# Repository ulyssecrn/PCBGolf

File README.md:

<div align="center">
<h1>My PCBGolf entry</h1>
<h3>comma.ai's PCBGolf challenge: a 4-port CAN-FD dev board on a 35 × 43 × 9.3 mm PCBA</h3>
<p>
  <a href="https://github.com/commaai/PCBGolf">Original challenge</a>
  <span> · </span>
  <a href="https://comma.ai/leaderboard#pcbgolf_challenge">Leaderboard</a>
  <span> · </span>
  <a href="https://kicanvas.org/?github=https%3A%2F%2Fgithub.com%2Fulyssecrn%2FPCBGolf%2Fblob%2Fmaster%2Fpcbgolf.kicad_pcb">View my layout in KiCanvas</a>
</p>
</div>

[PCBGolf](https://github.com/commaai/PCBGolf) is a challenge from comma.ai: take their reference board, loosely based on the panda jungle, and make the assembled PCBA as small as possible while keeping every interface working and every mating connector compatible. The board must be manufacturable and assemblable at JLCPCB. The score is

**bounding-box volume (mm³) + 50 × vias + 5,000 × copper layers**, lowest wins.

This repo is my submitted entry, finished on the October 12, 2026 deadline. The schematic is comma's. The layout, part choices and the design changes below are mine. comma's original README is kept unchanged [at the bottom](#original-challenge-readme).

## Result

| | |
|---|---|
| PCBA bounding box | 34.98 × 43.00 × 9.32 mm (includes the USB-C connector overhang) |
| Board outline | 33.9 × 42.3 mm, 0.79 mm thick |
| Copper layers | 4: signal / power / ground / signal |
| Vias | 303, all through-hole |
| Parts | 253, on both sides |
| **Score (by the formula)** | 14,027 + 15,150 + 20,000 = **≈ 49,200** |

The official score is assigned by comma after review.

<table>
  <tr>
    <td></td>
    <td></td>
  </tr>
  <tr>
    <td align="center">Top: connectors, CAN transceivers and chokes, power supplies</td>
    <td align="center">Bottom: STM32 (TFBGA-100), USB hub, microSD, port eFuses</td>
  </tr>
</table>

## What I changed

- **Stackup and placement.** 4 layers with an unbroken ground plane on In2. Parts on both sides: the STM32 and the USB hub on the bottom, the CAN transceivers and common-mode chokes on top, all six connectors on two edges.
- **MCU package: LQFP-144 → TFBGA-100.** I first tried the 7 × 7 mm UFBGA-169. At 0.5 mm pitch its inner balls carry signals and cannot be escaped on 4 layers without blind or buried vias. The 8 × 8 mm TFBGA-100 at 0.8 mm pitch escapes with ordinary dogbone vias.
- **Package change without touching the schematic.** The BGA footprint's pads are renamed to the LQFP-144 symbol's pin numbers, so comma's symbol keeps working and only the pins that don't exist on the smaller package needed rewiring.
- **Pin assignment as a routing tool.** Ports F and G aren't bonded out on TFBGA-100, so CAN2 moved to other FDCAN3 pins, and the SBU voltage-sense and current-monitor inputs moved to other ADC pins. I also re-ordered the 24 per-port control signals by channel so they leave the BGA in the same order as the connectors. All of this is a firmware pin-map change, which the rules allow (full table below).
- **Smaller parts.** 0201/0402 passives, 2016 crystals, smaller inductors, LEDs and dual FETs, a stemless 1.28 mm Molex microSD socket, and a TLV9101 (SC-70-5) in place of the SOT-23-5 op-amps that drive the CAN activity LEDs.

## Why the score isn't higher on the leaderboard

The penalties for layers and vias outweigh size. On this board, **layers (20,000) and vias (15,150) make up 71% of the score**, while the volume itself is only 14,027.

The top entries went the other way: one copper layer and no vias, with a board up to twice the area. Their fixed penalty is 5,000 instead of my 35,150. Once I had committed to a 4-layer board with a BGA, no amount of shrinking could close that gap. A 4-layer board scores 30,000+ before it has any volume at all.

**What I'd do differently:**
- Decide the layer count from the scoring formula first, and treat board area as the variable to give up.
- Pick an MCU package that can be routed on one or two layers (QFN/LQFP), even if it is larger.
- Watch the height. The DC barrel jack alone sets about 75% of the board's 9.3 mm height.

## Firmware changes

The MCU is an STM32H725VGH6 (TFBGA-100), the same die as the reference STM32H725ZGT (LQFP-144). Power, USB and clock setup are unchanged.

<details>
<summary>Pin map changes (reference → this board)</summary>

| Signal | Reference | This board | Notes |
|---|---|---|---|
| CAN2_TX / CAN2_RX | PG9 / PG10 | PD13 / PD12 | same FDCAN3 peripheral |
| BTN (GPIO read) | PE15 | PE5 | button still also drives BOOT0 |
| CH2_SBU2 sense | PF7 | PA3 | ADC12_INP15 (was ADC3) |
| CH4_SBU2 sense | PF8 | PA2 | ADC12_INP14 (was ADC3) |
| CH2_SBU1 sense | PF9 | PC5 | ADC12_INP8 (was ADC3) |
| CH4_SBU1 sense | PF10 | PB0 | ADC12_INP9 (was ADC3) |
| CH2_IMON | PB1 | PA6 | ADC12_INP3 |
| CH3_IMON | PF11 | PA5 | ADC12_INP19 |
| CH4_IMON | PA6 | PB1 | ADC12_INP5 |
| CH4_PWR_EN | PA5 | PA7 | |
| CH1_SBU1_IGN / RELAY | PD0 / PD1 | PD6 / PD3 | |
| CH1_SBU2_IGN | PD3 | PE0 | |
| CH2_SBU1_IGN / RELAY | PD5 / PD6 | PD1 / PE1 | |
| CH2_SBU2_IGN / RELAY | PD8 / PD10 | PD0 / PD5 | |
| CH3_SBU1_IGN / RELAY | PD12 / PD11 | PD14 / PD15 | |
| CH3_SBU2_IGN / RELAY | PD9 / PD13 | PE7 / PD11 | |
| CH4_SBU1_IGN / RELAY | PD14 / PD15 | PD9 / PE8 | |
| CH4_SBU2_IGN / RELAY | PE0 / PE1 | PD8 / PD10 | |

All other signals keep their reference pins.
</details>

## Files

- `pcbgolf.kicad_pro`: KiCad 10 project (the schematics are comma's, the layout is mine)
- `lib_jlc/`, `pcbgolf.pretty/`: footprints, symbols and 3D models; all paths are project-relative
- `assets/renders/`: the renders above, made with `kicad-cli pcb render`

<br>

---

*Everything below is comma.ai's original challenge README, unchanged.*

<div align="center">
<h1>PCBGolf Challenge</h1>
<h3>How small can you make this PCBA?</h3>
<h3>
  <a href="https://comma.ai/leaderboard#pcbgolf_challenge">Leaderboard</a>
  <span> · </span>
  <a href="https://comma.ai/jobs">comma.ai/jobs</a>
  <span> · </span>
  <a href="https://discord.comma.ai">Discord</a>
  <span> · </span>
  <a href="https://x.com/comma_ai">X</a>
</h3>
</div>

## The Board

The schematic is loosely based on [our panda jungle v2](https://www.comma.ai/shop/panda-jungle), a development and debugging board for comma devices and pandas. This version includes:

* 12V DC input with onboard 5V and 3.3V supplies
* Four [OBD-C](https://github.com/commaai/hardware/blob/master/harness/OBD-C.sch.pdf) device ports with individually controlled power and current monitoring
* Four CAN-FD transceivers and ignition simulation circuitry
* A USB hub and USB-C host connection
* A microcontroller and microSD card slot
* A push button and status LEDs

Explore in your browser with KiCanvas: [PCB layout](https://kicanvas.org/?github=https%3A%2F%2Fgithub.com%2Fcommaai%2FPCBGolf%2Fblob%2Fmaster%2Fpcbgolf.kicad_pcb).

Schematics: [Power](https://kicanvas.org/?github=https%3A%2F%2Fgithub.com%2Fcommaai%2FPCBGolf%2Fblob%2Fmaster%2Fpcbgolf.kicad_sch) · [Microcontroller](https://kicanvas.org/?github=https%3A%2F%2Fgithub.com%2Fcommaai%2FPCBGolf%2Fblob%2Fmaster%2Fpcbgolf_2.kicad_sch) · [USB & microSD](https://kicanvas.org/?github=https%3A%2F%2Fgithub.com%2Fcommaai%2FPCBGolf%2Fblob%2Fmaster%2Fpcbgolf_3.kicad_sch) · [CAN](https://kicanvas.org/?github=https%3A%2F%2Fgithub.com%2Fcommaai%2FPCBGolf%2Fblob%2Fmaster%2Fpcbgolf_4.kicad_sch) · [OBD-C ports](https://kicanvas.org/?github=https%3A%2F%2Fgithub.com%2Fcommaai%2FPCBGolf%2Fblob%2Fmaster%2Fpcbgolf_5.kicad_sch)

## The Challenge

Your goal is to make the most compact, efficient board that retains the same interfaces and functionality as the original design. The lowest score wins.

<p align="center">
  <picture>
    <source media="(prefers-color-scheme: dark)" srcset="./assets/score-dark.svg">
    
  </picture>
</p>

### Rules

* The bare PCB must be fully manufacturable by JLCPCB.
* It must be possible to actually assemble the PCBA.
* The assembled product must work and be usable.
* Mating connectors must remain mechanically and electrically compatible.
* Optimizations that require firmware changes are allowed.

### Prize

Lowest score on the [leaderboard](https://comma.ai/leaderboard#pcbgolf_challenge) by **October 12, 2026** wins **$1,000 cash**.

## Submission

Submit a `.zip` file containing your finalized KiCad project and a STEP file of the final assembly [here](https://forms.gle/US88Hg7UR6bBuW3BA).
Competitive scores will be posted on the [leaderboard](https://comma.ai/leaderboard#pcbgolf_challenge) after review. Multiple submissions allowed.

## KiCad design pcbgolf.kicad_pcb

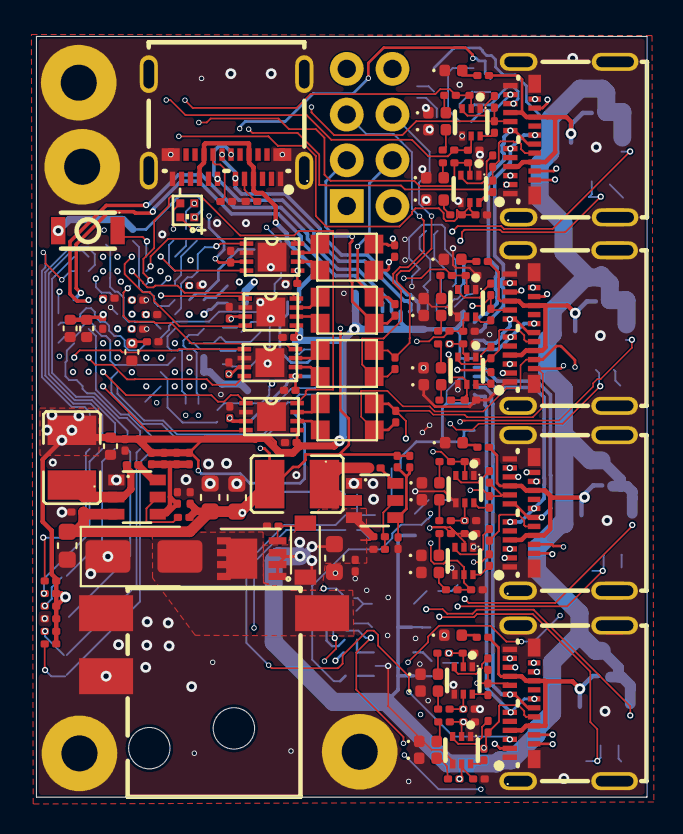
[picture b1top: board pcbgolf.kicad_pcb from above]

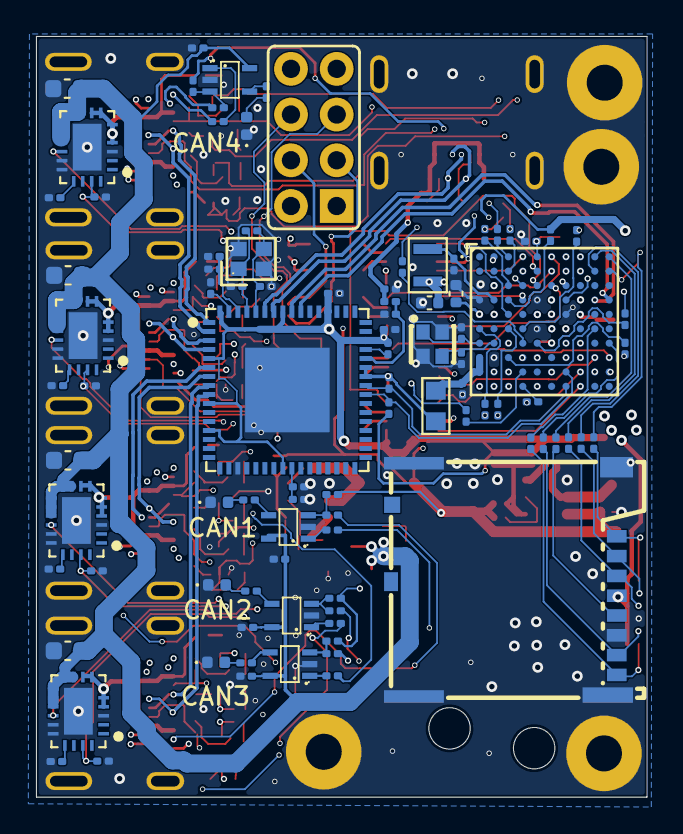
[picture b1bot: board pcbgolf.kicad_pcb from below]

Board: 4 copper layers, 33.9 x 42.3 mm, 253 parts (93 on the bottom side), 196 nets.

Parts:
BH1, BH2, BH3, BH4: M2_BOLT
C1, C3, C12, C13: 10uF; C_0603_1608Metric
C2, C4, C5, C7, C9, C11, C16, C18, C22, C23, C24, C26, C27, C30, C31, C35, C36, C38, C39, C40, C41, C42, C43, C44, C45, C46, C47, C48, C49, C55: 100nF; C_0201_0603Metric
C6, C10: DNP; C_0201_0603Metric
C8, C15, C19, C20, C21: 10uF; C_0402_1005Metric
C14, C17, C28, C32: 12pF; C_0201_0603Metric
C25: 220pF; C_0201_0603Metric
C29, C33, C34, C37: 10u; C_0201_0603Metric
C50, C51, C52, C53: 10u; C_0603_1608Metric
C54: 4.7uF; C_0402_1005Metric
D1: TVS-BI-DO214AA; D_SMA
D2: DIODEDB2W40100L; SOD-123F
J1: DCBARRELSMT; DC-IN-SMD_DC-044D-2.5A-2.0-SMT
J2: MICRO_SD-0472192001; microSD_Molex_5033981892
J3: USB-C-FEMALE; USB-C-J3-molex
J4: CAN; 2X04
J5, J6, J7, J8: USB-C-FEMALEGCT; USB-C-SMD_TYPE-C-USB-18
L1, L2: 3u3; IND_3225_3R3
L3: L-US-L2; 0603-L
L4: 2u2; 0806
L5, L6, L7, L8: ACT1210D_CHOKE; CHOKE-3.2X2.5
LED1: CREE-RGB-CLMVC; RGB_NH-B1010
LED2: CAN0; LED_0402_1005Metric
LED3: CAN1; LED_0402_1005Metric
LED4: CAN2; LED_0402_1005Metric
LED5: CAN3; LED_0402_1005Metric
LED6, LED7, LED8, LED9: CH1_PWR; LED_0402_1005Metric
LED10, LED11, LED12, LED13, LED14, LED15, LED16, LED17: LED_RED_0402; LED_0402_1005Metric
LED30, LED31, LED32, LED33, LED34, LED35, LED36, LED37: LED_GREEN_0402; LED_0402_1005Metric
Q1: SIS427-VI; PP-1212-8
Q2, Q3, Q4, Q5, Q6, Q7, Q8, Q9: NFET-DUAL-COMMON-SOURCE-QS5K2; SSM6N44FE-SOT563-remap
R1, R3, R7, R8, R9, R11, R12, R28, R29, R30, R33, R34, R35, R36, R37, R50, R51, R53, R54, R56, R57, R59, R60, R78, R79, R80, R81, R98, R99, R100, R101, R102, R103, R104, R105, R122, R123, R124, R125: 10k; R_0201_0603Metric
R2, R21, R23, R90, R92, R94, R96, R114, R116, R118, R120: 1k; R_0201_0603Metric
R4, R5, R6, R13, R14, R15, R16, R17, R18, R19, R20, R24, R25, R52, R55, R58, R61: 100k; R_0201_0603Metric
R10: 52k3; R_0201_0603Metric
R22, R62, R63, R64, R65: 2k7; R_0201_0603Metric
R26: 1M; R_0201_0603Metric
R27: 12k; R_0201_0603Metric
R32, R44: 5.1k; R_0201_0603Metric
R38, R39, R40, R41, R42, R43: 0R; R_0201_0603Metric
R46, R47, R48, R49: 60; R_0201_0603Metric
R66, R67, R68, R69: 28k; R_0201_0603Metric
R70, R71, R72, R73: 33k; R_0201_0603Metric
R74, R75, R76, R77: 3k3; R_0201_0603Metric
R82, R83, R84, R85, R86, R87, R88, R89, R91, R93, R95, R97, R106, R107, R108, R109, R110, R111, R112, R113, R115, R117, R119, R121: 100; R_0201_0603Metric
SW1: SPST-2-4PIN; SW_TS2306A
U1, U2: AP62300T; SOT23-6
U3: STM32H725VGH6; STM32H725-TFBGA100-remap
U4: USB2517; QFN64-9X9
U5, U6, U7, U8: MCP2542FDT-E/MNY; TDFN8_2X3MC_MCH
U13, U14, U15, U16: TPS25942; WQFN20
U17, U18, U19, U20: TLV9101IDCKR; TLV9101-SC70-5
Y1: 25MHz; Crystal_2016_25M
Y2: 24MHz; Crystal_2016_24M

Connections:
+3V3: C6.2, C7.1, C8.1, C19.1, C20.1, C23.1, C24.1, C26.1, C27.1, C30.2, C31.2, C37.1, C42.1, C43.1, C44.1, C45.1, C54.1, C55.1, J2.4 (VDD), L1.2, L3.1, LED1.U1 (COM+), R4.1, R5.1, R6.1, R11.1, R28.1, R29.1, R30.1, R33.1, R34.1, R35.1, R36.1, R37.1, SW1.B (S), SW1.B' (S1), U3.7 (VDD), U3.8 (VBAT), U3.13 (VDD), U3.16 (VDDSMPS), U3.19 (VDD), U3.91 (VDD33USB), U4.5 (VDDA33), U4.10 (VDDA33), U4.13 (CFG_SEL2), U4.24 (VDD33CR), U4.42 (CFG_SEL1), U4.43 (RESET_N), U4.46 (VDD33), U4.52 (VDDA33), U4.57 (VDDA33), U4.64 (VDD33PLL), U5.5 (VIO), U6.5 (VIO), U7.5 (VIO), U8.5 (VIO)
+5V: C1.1, C2.1, C10.2, C11.1, C12.1, C13.1, C38.1, C39.1, C40.1, C41.1, L2.2, R1.1, R10.2, R52.2, R55.2, R58.2, R61.2, U1.3 (IN), U5.3 (VDD), U6.3 (VDD), U7.3 (VDD), U8.3 (VDD)
+12V: C3.1, C5.1, C46.1, C47.1, C48.1, C49.1, C50.1, C51.1, C52.1, C53.1, D2.1 (C), Q1.1 (S), Q1.2 (S), Q1.3 (S), R7.1, U2.3 (IN), U13.9 (VIN), U13.10 (VIN), U13.11 (VIN), U13.12 (VIN), U13.13 (VIN), U14.9 (VIN), U14.10 (VIN), U14.11 (VIN), U14.12 (VIN), U14.13 (VIN), U15.9 (VIN), U15.10 (VIN), U15.11 (VIN), U15.12 (VIN), U15.13 (VIN), U16.9 (VIN), U16.10 (VIN), U16.11 (VIN), U16.12 (VIN), U16.13 (VIN), U17.5 (V+), U18.5 (V+), U19.5 (V+), U20.5 (V+)
BTN: R12.2, SW1.A, SW1.A' (P1), U3.4 (PE5), U3.135 (BOOT0)
CAN0_EN: U3.134 (PB7), U5.8 (STBY)
CAN0_H: J4.2, J5.A2 (TX1+), J6.A2 (TX1+), J7.A2 (TX1+), J8.A2 (TX1+), L5.4, R46.2, R50.1
CAN0_L: J4.1, J5.A3 (TX1-), J6.A3 (TX1-), J7.A3 (TX1-), J8.A3 (TX1-), L5.3, R46.1, R51.1
CAN0_RX: U3.136 (PB8), U5.4 (RXD)
CAN0_TX: U3.137 (PB9), U5.1 (TXD)
CAN1_EN: U3.130 (PB3(JTDO), U6.8 (STBY)
CAN1_H: J4.4, J5.A11 (RX2+), J6.A11 (RX2+), J7.A11 (RX2+), J8.A11 (RX2+), L6.4, R47.2, R53.1
CAN1_L: J4.3, J5.A10 (RX2-), J6.A10 (RX2-), J7.A10 (RX2-), J8.A10 (RX2-), L6.3, R47.1, R54.1
CAN1_RX: U3.132 (PB5), U6.4 (RXD)
CAN1_TX: U3.133 (PB6), U6.1 (TXD)
CAN2_EN: U3.121 (PD7), U7.8 (STBY)
CAN2_H: J4.6, J5.B2 (TX2+), J6.B2 (TX2+), J7.B2 (TX2+), J8.B2 (TX2+), L7.4, R48.2, R56.1
CAN2_L: J4.5, J5.B3 (TX2-), J6.B3 (TX2-), J7.B3 (TX2-), J8.B3 (TX2-), L7.3, R48.1, R57.1
CAN2_RX: U3.82 (PD12), U7.4 (RXD)
CAN2_TX: U3.83 (PD13), U7.1 (TXD)
CAN3_EN: U3.131 (PB4(NJTRST)), U8.8 (STBY)
CAN3_H: J4.8, J5.B11 (RX1+), J6.B11 (RX1+), J7.B11 (RX1+), J8.B11 (RX1+), L8.4, R49.2, R59.1
CAN3_L: J4.7, J5.B10 (RX1-), J6.B10 (RX1-), J7.B10 (RX1-), J8.B10 (RX1-), L8.3, R49.1, R60.1
CAN3_RX: U3.72 (PB12), U8.4 (RXD)
CAN3_TX: U3.73 (PB13), U8.1 (TXD)
CH1_D_N: J5.A7 (D-A), J5.B7 (D-B), U4.1 (USBDN1_DM)
CH1_D_P: J5.A6 (D+A), J5.B6 (D+B), U4.2 (USBDN1_DP)
CH1_IMON: R70.2, U3.47 (PC4), U13.19 (IMON)
CH1_PWR_EN: U3.37 (PA0), U13.14 (EN)
CH1_SBU1: J5.A8 (SBU1), R19.2, R90.2, R91.2
CH1_SBU1_IGN: Q2.1 (G1), R78.1, R83.2, U3.120 (PD6)
CH1_SBU1_RELAY: Q2.3 (G2), R82.2, R98.2, U3.115 (PD3)
CH1_SBU2: J5.B8 (SBU2), R20.2, R114.2, R115.2
CH1_SBU2_IGN: Q6.1 (G1), R102.1, R107.2, U3.138 (PE0)
CH1_SBU2_RELAY: Q6.3 (G2), R106.2, R122.2, U3.116 (PD4)
CH2_D_N: J6.A7 (D-A), J6.B7 (D-B), U4.3 (USBDN2_DM)
CH2_D_P: J6.A6 (D+A), J6.B6 (D+B), U4.4 (USBDN2_DP)
CH2_IMON: R71.2, U3.45 (PA6), U14.19 (IMON)
CH2_PWR_EN: U3.38 (PA1), U14.14 (EN)
CH2_SBU1: J6.A8 (SBU1), R15.2, R92.2, R93.2
CH2_SBU1_IGN: Q3.1 (G1), R79.1, R85.2, U3.113 (PD1)
CH2_SBU1_RELAY: Q3.3 (G2), R84.2, R99.2, U3.139 (PE1)
CH2_SBU1_SENSE: R15.1, U3.48 (PC5)
CH2_SBU2: J6.B8 (SBU2), R13.2, R116.2, R117.2
CH2_SBU2_IGN: Q7.1 (G1), R103.1, R109.2, U3.112 (PD0)
CH2_SBU2_RELAY: Q7.3 (G2), R108.2, R123.2, U3.117 (PD5)
CH2_SBU2_SENSE: R13.1, U3.40 (PA3)
CH3_D_N: J7.A7 (D-A), J7.B7 (D-B), U4.6 (USBDN3_DM)
CH3_D_P: J7.A6 (D+A), J7.B6 (D+B), U4.7 (USBDN3_DP)
CH3_IMON: R72.2, U3.44 (PA5), U15.19 (IMON)
CH3_PWR_EN: U3.43 (PA4), U15.14 (EN)
CH3_SBU1: J7.A8 (SBU1), R17.2, R94.2, R95.2
CH3_SBU1_IGN: Q4.1 (G1), R80.1, R87.2, U3.84 (PD14)
CH3_SBU1_RELAY: Q4.3 (G2), R86.2, R100.2, U3.85 (PD15)
CH3_SBU2: J7.B8 (SBU2), R18.2, R118.2, R119.2
CH3_SBU2_IGN: Q8.1 (G1), R104.1, R111.2, U3.57 (PE7)
CH3_SBU2_RELAY: Q8.3 (G2), R110.2, R124.2, U3.81 (PD11)
CH4_D_N: J8.A7 (D-A), J8.B7 (D-B), U4.8 (USBDN4_DM)
CH4_D_P: J8.A6 (D+A), J8.B6 (D+B), U4.9 (USBDN4_DP)
CH4_IMON: R73.2, U3.50 (PB1), U16.19 (IMON)
CH4_PWR_EN: U3.46 (PA7), U16.14 (EN)
CH4_SBU1: J8.A8 (SBU1), R16.2, R96.2, R97.2
CH4_SBU1_IGN: Q5.1 (G1), R81.1, R89.2, U3.77 (PD9)
CH4_SBU1_RELAY: Q5.3 (G2), R88.2, R101.2, U3.58 (PE8)
CH4_SBU1_SENSE: R16.1, U3.49 (PB0)
CH4_SBU2: J8.B8 (SBU2), R14.2, R120.2, R121.2
CH4_SBU2_IGN: Q9.1 (G1), R105.1, R113.2, U3.76 (PD8)
CH4_SBU2_RELAY: Q9.3 (G2), R112.2, R125.2, U3.78 (PD10)
CH4_SBU2_SENSE: R14.1, U3.39 (PA2)
GND: BH1.0 (1_0), BH2.0 (1_0), BH3.0 (1_0), BH4.0 (1_0), C1.2, C2.2, C3.2, C5.2, C7.2, C8.2, C11.2, C12.2, C13.2, C14.2, C15.2, C16.2, C17.2, C18.2, C19.2, C20.2, C21.2, C22.2, C23.2, C24.2, C25.2, C26.2, C27.2, C28.2, C29.2, C30.1, C31.1, C32.2, C33.2, C34.2, C35.1, C36.1, C37.2, C38.2, C39.2, C40.2, C41.2, C42.2, C43.2, C44.2, C45.2, C46.2, C47.2, C48.2, C49.2, C50.2, C51.2, C52.2, C53.2, C54.2, C55.2, D1.1, J1.GND (GNDBREAK), J1.GNDBREAK (GND), J2.6 (VSS), J2.G1 (GND), J2.G2 (GND), J2.G3 (GND), J2.G4 (GND), J3.A1 (GND), J3.A12 (GND), J3.B1 (GND), J3.B1T (GND), J3.B12 (GND), J3.B12T (GND), J3.S1B (SHIELDA), J3.S1T (SHIELDA), J3.S1TH (SHIELDA), J3.S2B (SHIELDA), J3.S2T (SHIELDA), J3.S2TH (SHIELDA), J3.S3B (SHIELDB), J3.S3T (SHIELDB), J3.S3TH (SHIELDB), J3.S4B (SHIELDB), J3.S4T (SHIELDB), J3.S4TH (SHIELDB), J5.A1 (GND), J5.A12 (GND), J5.B1 (GND), J5.B12 (GND), J5.S1 (SHIELDA), J5.S2 (SHIELDA), J5.S3 (SHIELDA), J5.S4 (SHIELDA), J5.S11 (SHIELDB), J5.S12 (SHIELDB), J5.S13 (SHIELDB), J5.S14 (SHIELDB), J6.A1 (GND), J6.A12 (GND), J6.B1 (GND), J6.B12 (GND), J6.S1 (SHIELDA), J6.S2 (SHIELDA), J6.S3 (SHIELDA), J6.S4 (SHIELDA), J6.S11 (SHIELDB), J6.S12 (SHIELDB), J6.S13 (SHIELDB), J6.S14 (SHIELDB), J7.A1 (GND), J7.A12 (GND), J7.B1 (GND), J7.B12 (GND), J7.S1 (SHIELDA), J7.S2 (SHIELDA), J7.S3 (SHIELDA), J7.S4 (SHIELDA), J7.S11 (SHIELDB), J7.S12 (SHIELDB), J7.S13 (SHIELDB), J7.S14 (SHIELDB), J8.A1 (GND), J8.A12 (GND), J8.B1 (GND), J8.B12 (GND), J8.S1 (SHIELDA), J8.S2 (SHIELDA), J8.S3 (SHIELDA), J8.S4 (SHIELDA), J8.S11 (SHIELDB), J8.S12 (SHIELDB), J8.S13 (SHIELDB), J8.S14 (SHIELDB), LED2.C, LED3.C, LED4.C, LED5.C, LED6.C, LED7.C, LED8.C, LED9.C, LED10.C, LED11.C, LED12.C, LED13.C, LED14.C, LED15.C, LED16.C, LED17.C, LED30.C, LED31.C, LED32.C, LED33.C, LED34.C, LED35.C, LED36.C, LED37.C, Q2.2 (S), Q3.2 (S), Q4.2 (S), Q5.2 (S), Q6.2 (S), Q7.2 (S), Q8.2 (S), Q9.2 (S), R2.1, R3.2, R8.2, R9.2, R12.1, R25.1, R27.1, R32.2, R44.2, R66.1, R67.1, R68.1, R69.1, R70.1, R71.1, R72.1, R73.1, R78.2, R79.2, R80.2, R81.2, R98.1, R99.1, R100.1, R101.1, R102.2, R103.2, R104.2, R105.2, R122.1, R123.1, R124.1, R125.1, U1.1 (GND), U2.1 (GND), U3.6 (VSS), U3.12 (VSS), U3.14 (VSSSMPS), U3.18 (VSS), U3.33 (VSS), U3.34 (VSSA), U4.19 (TEST), U4.PAD (VSS), U5.2 (VSS), U5.PAD (EPAD), U6.2 (VSS), U6.PAD (EPAD), U7.2 (VSS), U7.PAD (EPAD), U8.2 (VSS), U8.PAD (EPAD), U13.3 (PGTH), U13.15 (OVP), U13.16 (GND), U13.PAD (GND), U14.3 (PGTH), U14.15 (OVP), U14.16 (GND), U14.PAD (GND), U15.3 (PGTH), U15.15 (OVP), U15.16 (GND), U15.PAD (GND), U16.3 (PGTH), U16.15 (OVP), U16.16 (GND), U16.PAD (GND), U17.2 (V-), U18.2 (V-), U19.2 (V-), U20.2 (V-), Y1.2 (3), Y1.4 (3), Y2.2 (3), Y2.4 (3)
HUB_SCL: R30.2, U3.66 (PB10), U4.41 (SCL)
HUB_SDA: R28.2, U3.67 (PB11), U4.40 (SDA)
LED_B: R23.2, U3.1 (PE2)
LED_G: R22.2, U3.2 (PE3)
LED_R: R21.2, U3.3 (PE4)
unnamed: D2.2 (A), Q1.4 (G), R2.2
unnamed: D1.2, J1.PWR1 (PWR), Q1.5 (D), Q1.6 (D), Q1.7 (D), Q1.8 (D), Q1.9 (D)
unnamed: J2.2 (CD/DAT3), R36.2, R41.2
unnamed: J2.5 (CLK), R43.2
unnamed: J2.3 (CMD), R37.2, R42.2
unnamed: J2.7 (DAT0), R33.2, R38.2
unnamed: J2.8 (DAT1), R34.2, R39.2
unnamed: J2.1 (DAT2), R35.2, R40.2
unnamed: J3.A5 (CC1), R32.1
unnamed: J3.B5 (CC2), J3.B5T (CC2), R44.1
unnamed: J3.B11 (RX1+), J3.B11T (RX1+)
unnamed: J3.B10 (RX1-), J3.B10T (RX1-)
unnamed: J3.B8 (SBU2), J3.B8T (SBU2)
unnamed: J3.B2 (TX2+), J3.B2T (TX2+)
unnamed: J3.B3 (TX2-), J3.B3T (TX2-)
unnamed: J5.A4 (VBUS), J5.A9 (VBUS), J5.B4 (VBUS), J5.B9 (VBUS), R74.1, U13.4 (VOUT), U13.5 (VOUT), U13.6 (VOUT), U13.7 (VOUT), U13.8 (VOUT)
unnamed: J6.A4 (VBUS), J6.A9 (VBUS), J6.B4 (VBUS), J6.B9 (VBUS), R75.1, U14.4 (VOUT), U14.5 (VOUT), U14.6 (VOUT), U14.7 (VOUT), U14.8 (VOUT)
unnamed: J7.A4 (VBUS), J7.A9 (VBUS), J7.B4 (VBUS), J7.B9 (VBUS), R76.1, U15.4 (VOUT), U15.5 (VOUT), U15.6 (VOUT), U15.7 (VOUT), U15.8 (VOUT)
unnamed: J8.A4 (VBUS), J8.A9 (VBUS), J8.B4 (VBUS), J8.B9 (VBUS), R77.1, U16.4 (VOUT), U16.5 (VOUT), U16.6 (VOUT), U16.7 (VOUT), U16.8 (VOUT)
unnamed: LED1.U4 (B-), R23.1
unnamed: LED1.U3 (G-), R22.1
unnamed: LED1.U2 (R-), R21.1
unnamed: LED2.A, R62.2
unnamed: LED3.A, R63.2
unnamed: LED4.A, R64.2
unnamed: LED5.A, R65.2
unnamed: LED6.A, R74.2
unnamed: LED7.A, R75.2
unnamed: LED8.A, R76.2
unnamed: LED9.A, R77.2
unnamed: LED10.A, R83.1
unnamed: LED11.A, R85.1
unnamed: LED12.A, R87.1
unnamed: LED13.A, R89.1
unnamed: LED14.A, R107.1
unnamed: LED15.A, R109.1
unnamed: LED16.A, R111.1
unnamed: LED17.A, R113.1
unnamed: LED30.A, R82.1
unnamed: LED31.A, R84.1
unnamed: LED32.A, R86.1
unnamed: LED33.A, R88.1
unnamed: LED34.A, R106.1
unnamed: LED35.A, R108.1
unnamed: LED36.A, R110.1
unnamed: LED37.A, R112.1
unnamed: Q2.5 (D1), R90.1
unnamed: Q2.4 (D2), R91.1
unnamed: Q3.5 (D1), R92.1
unnamed: Q3.4 (D2), R93.1
unnamed: Q4.5 (D1), R94.1
unnamed: Q4.4 (D2), R95.1
unnamed: Q5.5 (D1), R96.1
unnamed: Q5.4 (D2), R97.1
unnamed: Q6.5 (D1), R114.1
unnamed: Q6.4 (D2), R115.1
unnamed: Q7.5 (D1), R116.1
unnamed: Q7.4 (D2), R117.1
unnamed: Q8.5 (D1), R118.1
unnamed: Q8.4 (D2), R119.1
unnamed: Q9.5 (D1), R120.1
unnamed: Q9.4 (D2), R121.1
unnamed: C4.1, U1.6 (BST)
unnamed: R1.2, U1.5 (EN)
unnamed: C6.1, R3.1, R4.2, R5.2, R6.2, U1.4 (FB)
unnamed: C4.2, L1.1, U1.2 (SW)
unnamed: C9.1, U2.6 (BST)
unnamed: R7.2, R8.1, U2.5 (EN)
unnamed: C10.1, R9.1, R10.1, U2.4 (FB)
unnamed: C9.2, L2.1, U2.2 (SW)
unnamed: R17.1, U3.28 (PC0)
unnamed: R18.1, U3.29 (PC1)
unnamed: R19.1, U3.30 (PC2_C)
unnamed: R20.1, U3.31 (PC3_C)
unnamed: R11.2, U3.142 (PDR_ON)
unnamed: C14.1, U3.25 (PH0), Y1.1
unnamed: C17.1, U3.26 (PH1), Y1.3 (2)
unnamed: R27.2, U4.63 (RBIAS)
unnamed: R29.2, U4.45 (SUSP_IND)
unnamed: R24.1, R25.2, U4.44 (VBUS_DET)
unnamed: C33.1, C35.2, U4.25 (VDD18)
unnamed: C34.1, C36.2, U4.62 (VDD18PLL)
unnamed: C28.1, R26.2, U4.61 (XTAL1), Y2.1
unnamed: C32.1, R26.1, U4.60 (XTAL2), Y2.3 (2)
unnamed: L5.1, U5.7 (CANH)
unnamed: L5.2, U5.6 (CANL)
unnamed: L6.1, U6.7 (CANH)
unnamed: L6.2, U6.6 (CANL)
unnamed: L7.1, U7.7 (CANH)
unnamed: L7.2, U7.6 (CANL)
unnamed: L8.1, U8.7 (CANH)
unnamed: L8.2, U8.6 (CANL)
unnamed: R66.2, U13.17 (ILIM)
unnamed: R67.2, U14.17 (ILIM)
unnamed: R68.2, U15.17 (ILIM)
unnamed: R69.2, U16.17 (ILIM)
unnamed: R50.2, U17.1 (IN+)
unnamed: R51.2, R52.1, U17.3 (IN−)
unnamed: R62.1, U17.4 (OUT)
unnamed: R53.2, U18.1 (IN+)
unnamed: R54.2, R55.1, U18.3 (IN−)
unnamed: R63.1, U18.4 (OUT)
unnamed: R56.2, U19.1 (IN+)
unnamed: R57.2, R58.1, U19.3 (IN−)
unnamed: R64.1, U19.4 (OUT)
unnamed: R59.2, U20.1 (IN+)
unnamed: R60.2, R61.1, U20.3 (IN−)
unnamed: R65.1, U20.4 (OUT)
SD_CLK: R43.1, U3.111 (PC12)
SD_CMD: R42.1, U3.114 (PD2)
SD_D0: R38.1, U3.95 (PC8)
SD_D1: R39.1, U3.96 (PC9)
SD_D2: R40.1, U3.109 (PC10)
SD_D3: R41.1, U3.110 (PC11)
STM_D_N: U3.100 (PA11), U4.55 (USBDN7_DM)
STM_D_P: U3.101 (PA12), U4.56 (USBDN7_DP)
USB_D_N: J3.A7 (D-A), J3.B7 (D-B), J3.B7T (D-B), U4.58 (USBUP_DM)
USB_D_P: J3.A6 (D+A), J3.B6 (D+B), J3.B6T (D+B), U4.59 (USBUP_DP)
VBUS: C29.1, J3.A4 (VBUS), J3.A9 (VBUS), J3.B4 (VBUS), J3.B4T (VBUS), J3.B9 (VBUS), J3.B9T (VBUS), R24.2
VDDA: C22.1, L3.2, U3.35 (VREF+), U3.36 (VDDA)
VDDLDO: C15.1, C16.1, C18.1, C21.1, L4.1, U3.17 (VFBSMPS), U3.68 (VCAP), U3.70 (VDDLDO), U3.103 (VCAP), U3.105 (VDDLDO)
VLXSMPS: C25.1, L4.2, U3.15 (VLXSMPS)
